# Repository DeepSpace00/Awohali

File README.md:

# ᎠᏬᎭᎵ (Awohali)

Pronounced (Ah-wo-ha-lee)

This project is archived. Current development has migrated to [Codeberg](https://codeberg.org/Fiducial-Systems/Awohali)

An open source hardware GNSS receiver station for measuring tropospheric precipitable water vapor.

A master's thesis project within Embry-Riddle Aeronautical University's Physical Science Department.

⚠️ WARNING This project is currently under development ⚠️

## Docs

https://deepspace00.github.io/Awohali/

## Hardware 

Preview with [KiCanvas](https://kicanvas.org/?github=https%3A%2F%2Fgithub.com%2FDeepSpace00%2FAwohali%2Ftree%2Fmain%2Fhardware%2Felectronics%2FmainBoard)

## Licenses

Documentation, firmware, hardware, and software are individually licensed. Terms and conditions apply within their respective folders.

**Documentation -** [Apache License 2.0](docs/LICENSE)

**Firmware/Software -** [The MIT License](firmware/LICENSE)

**Hardware -** [CERN-OHL-P v2 or later](hardware/LICENSE)

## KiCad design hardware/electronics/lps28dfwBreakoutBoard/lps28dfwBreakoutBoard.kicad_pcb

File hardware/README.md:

Copyright Madison Gleydura 2025.

This source describes Open Hardware and is licensed under the CERN-OHL-P v2

You may redistribute and modify this documentation and make products
using it under the terms of the [CERN-OHL-P v2](LICENSE).
This documentation is distributed WITHOUT ANY EXPRESS OR IMPLIED
WARRANTY, INCLUDING OF MERCHANTABILITY, SATISFACTORY QUALITY
AND FITNESS FOR A PARTICULAR PURPOSE. Please see the CERN-OHL-P v2
for applicable conditions

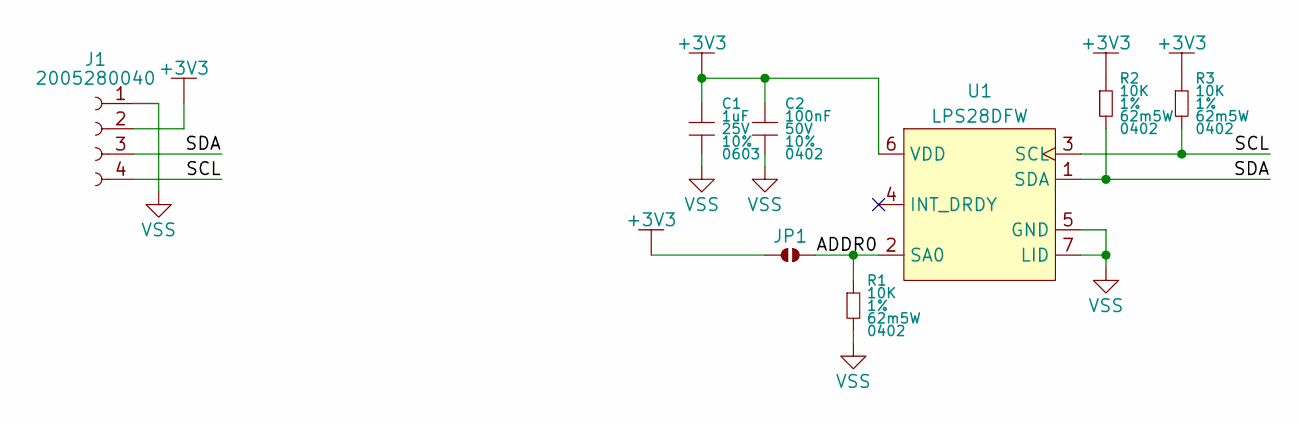
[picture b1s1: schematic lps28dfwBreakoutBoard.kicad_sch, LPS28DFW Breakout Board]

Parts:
C1: 1uF; GRT0603; Tolerance 10%; Voltage Rating 25V; MPN GRT188R71E105KE13D
C2: 100nF; GCM0402; Tolerance 10%; Voltage Rating 50V; MPN GRT155R71H104KE01D
J1: 2005280040; MPN 2005280040
JP1: SolderJumper-2_P1.3mm_Open_TrianglePad1.0x1.5mm
R1, R2, R3: 10K; CRCW0402; Tolerance 1%; Power Rating 62m5W; MPN CRCW040210K0FKED
U1: LPS28DFW; CCLGA7_LPS28DFWTR; MPN LPS28DFWTR

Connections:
+3V3: C1.1, C2.1, J1.2, JP1.1, R2.1, R3.1, U1.6 (VDD)
/ADDR0: JP1.2, R1.1, U1.2 (SA0)
/SCL: J1.4, R3.2, U1.3 (SCL)
/SDA: J1.3, R2.2, U1.1 (SDA)
VSS: C1.2, C2.2, J1.1, R1.2, U1.5 (GND), U1.7 (LID)

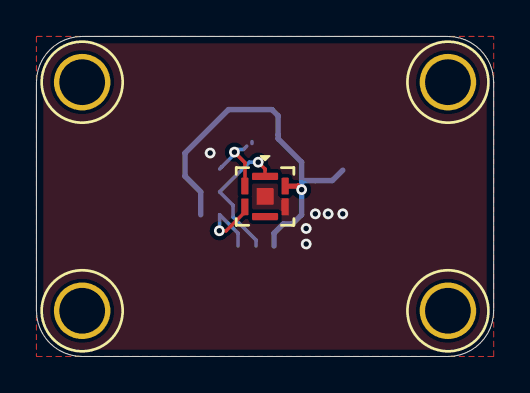
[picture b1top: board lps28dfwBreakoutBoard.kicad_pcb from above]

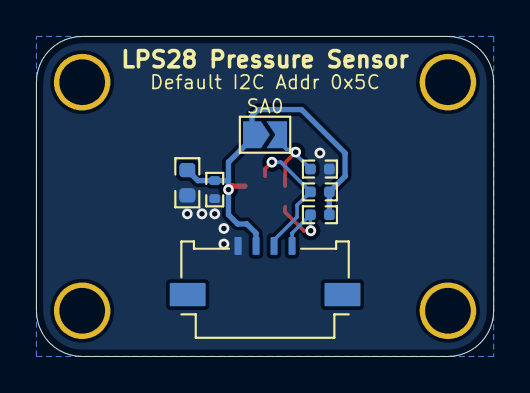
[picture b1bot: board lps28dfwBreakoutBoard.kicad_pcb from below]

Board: 2 copper layers, 25.4 x 17.8 mm, 8 parts (7 on the bottom side), 5 nets.

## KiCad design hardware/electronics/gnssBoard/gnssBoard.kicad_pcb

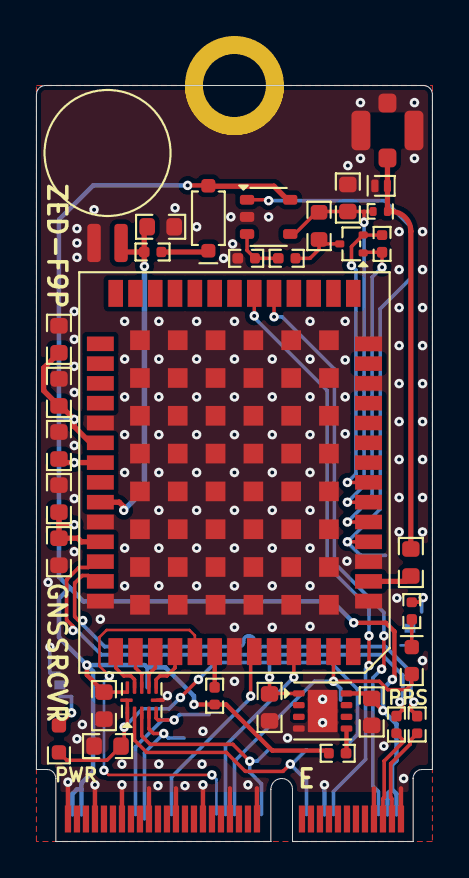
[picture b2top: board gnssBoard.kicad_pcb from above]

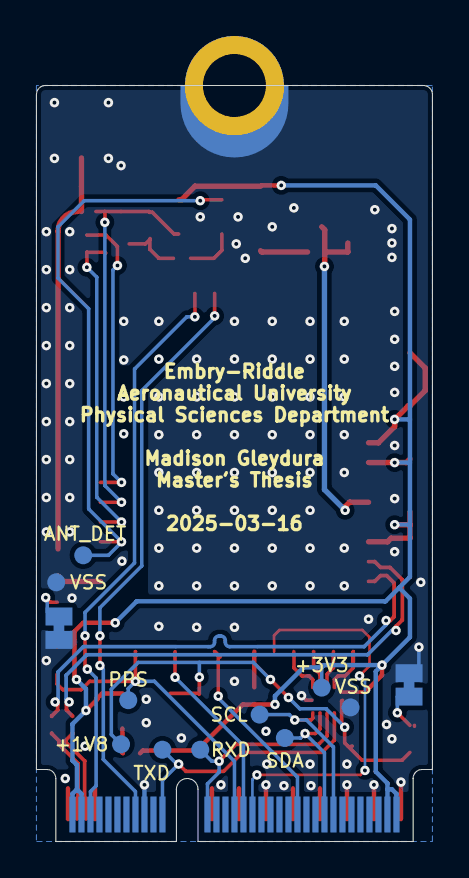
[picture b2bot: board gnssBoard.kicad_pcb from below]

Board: 4 copper layers, 22.0 x 42.0 mm, 48 parts (12 on the bottom side), 36 nets.

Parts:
AE1: CONMHF1-SMD-T; CONMHF1
BT1: MS621FE-FL11E
C1, C2, C9: 2.2uF; MLCC0603
C3: 47pF; MLCC0603
C4, C7: 1uF; MLCC0603
C5, C6, C8, C11, C12: 100nF; MLCC0603
C10: 10nF; MLCC0603
D1: LTST-C190KYKT; LTST-0603
D2: B0540WQ; SOD123
D3: PTVS4V5D1BLYL; SOD882
D4: LTST-C190KRKT; LTST-0603
J1: Standoff; M.2-Screw-Pad
J2: M.2_E_Key_PCB_Edge; M.2 E-Key
JP1, JP2: SolderJumper-2_P1.3mm_Bridged_Pad1.0x1.5mm
L1: 47nH; L_0402
Q1: DMG1013TQ-7; SOT23-3P50_160X160X75L22X22N
R1, R8, R11: 10K; CRCW0402
R4: 3K3; CRCW0402
R5: 10R; CRCW0603
R6: 100R; CRCW0402
R7, R9: 27R; CRCW0402
R10: 1K; CRCW0402
R12: 100K; CRCW0402
TP1: +3V3; TP_1mm
TP2: +1V8; TP_1mm
TP3, TP11: VSS; TP_1mm
TP4: SCL; TP_1mm
TP5: SDA; TP_1mm
TP6: TXD; TP_1mm
TP7: RXD; TP_1mm
TP9: PPS; TP_1mm
TP10: ANT_DET; TP_1mm
U1: AP7361E; UDFN8P65_300X300X60L25X45L
U2: TXS0104VxRUTR; RUT0012A
U3: ZED-F9P; ZED-F9P-04B_UBL
U4: OPA344; SOT23-5P95_280X300X110L40X38N

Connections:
+1V8: C2.1, C11.1, D1.1, TP2.1, U1.1 (OUT), U2.1 (VCCA), U2.12 (OE)
+3V3: C1.1, C4.1, C5.1, C6.1, C7.1, C8.1, C12.1, D2.1, J2.2 (3.3V), J2.4 (3.3V), J2.72 (3.3V), J2.74 (3.3V), R1.1, R11.1, TP1.1, U1.8 (IN), U2.11 (VCCB), U3.33 (VCC), U3.34 (VCC), U3.38 (V_USB), U4.5 (V+)
/ANT_DET: TP10.1, U3.4 (ANT_DET), U4.1
/ANT_IN: AE1.1 (A), C3.1, D3.2, L1.1
/ANT_OFF: Q1.1, R8.2, U3.5 (ANT_OFF)
/ANT_SHORT_N: C10.1, L1.2, R5.1, U3.6 (ANT_SHORT_N), U4.4 (-)
/EXTINT: J2.40 (VENDOR_DEFINED), U3.51 (EXTINT)
/GEOFENCE_STAT: J2.6 (~LED_1), U3.19 (GEOFENCE_STAT)
/HOST_D+: J2.3 (USB_D+), R7.1
/HOST_D-: J2.5 (USB_D-), R9.1
/PPS: D4.1, J2.38 (VENDOR_DEFINED), TP9.1, U3.53 (TIMEPULSE)
/RESET_N: J2.52 (~PERST0), U3.49 (RESET_N)
/RF_IN: C3.2, U3.2 (RF_IN)
/RTK_STAT: J2.16 (~LED_2), U3.20 (RTK_STAT)
/SCL_1V8: J2.60 (I2C_CLK), TP4.1, U2.5 (A4)
/SCL_3V3: U2.7 (B4), U3.45 (SCL)
/SDA_1V8: J2.58 (I2C_DATA), TP5.1, U2.4 (A3)
/SDA_3V3: U2.8 (B3), U3.44 (SDA)
/TX_RDY: J2.42 (VENDOR_DEFINED), U3.46 (TX_RDY)
/ZED_D+: R7.2, U3.40 (USB_DP)
/ZED_D-: R9.2, U3.39 (USB_DM)
/ZED_RXD_1V8: J2.32 (UART_TXD), TP7.1, U2.3 (A2)
/ZED_RXD_3V3: U2.9 (B2), U3.43 (RXD)
/ZED_TXD_1V8: J2.22 (UART_RXD), TP6.1, U2.2 (A1)
/ZED_TXD_3V3: U2.10 (B1), U3.42 (TXD)
unnamed: D1.2, JP1.2
unnamed: D2.2, R4.1
unnamed: D4.2, R6.2
unnamed: JP2.1, R6.1
unnamed: Q1.3, R5.2, R10.1
unnamed: R1.2, U1.5 (EN)
unnamed: R11.2, U3.47 (D_SEL)
unnamed: R10.2, R12.1, U4.3 (+)
VBAT: BT1.1, C9.1, R4.2, U3.36 (V_BCKP)
VCC_RF: Q1.2, R8.1, U3.7 (VCC_RF)
VSS: AE1.2 (Shield), BT1.2, C1.2, C2.2, C4.2, C5.2, C6.2, C7.2, C8.2, C9.2, C10.2, C11.2, C12.2, D3.1, J1.1, J2.1 (GND), J2.7 (GND), J2.18 (GND), J2.33 (GND), J2.39 (GND), J2.45 (GND), J2.51 (GND), J2.57 (GND), J2.63 (GND), J2.69 (GND), J2.75 (GND), JP1.1, JP2.2, R12.2, TP3.1, TP11.1, U1.4 (GND), U1.9 (GND), U2.6 (GND), U3.1 (GND), U3.3 (GND), U3.12 (GND), U3.14 (GND), U3.32 (GND), U3.37 (GND), U3.41 (GND), U3.48 (GND), U3.55 (PGND), U3.56 (PGND), U3.57 (PGND), U3.58 (PGND), U3.59 (PGND), U3.60 (PGND), U3.61 (PGND), U3.62 (PGND), U3.63 (PGND), U3.64 (PGND), U3.65 (PGND), U3.66 (PGND), U3.67 (PGND), U3.68 (PGND), U3.69 (PGND), U3.70 (PGND), U3.71 (PGND), U3.72 (PGND), U3.73 (PGND), U3.74 (PGND), U3.75 (PGND), U3.76 (PGND), U3.77 (PGND), U3.78 (PGND), U3.79 (PGND), U3.80 (PGND), U3.81 (PGND), U3.82 (PGND), U3.83 (PGND), U3.84 (PGND), U3.85 (PGND), U3.86 (PGND), U3.87 (PGND), U3.88 (PGND), U3.89 (PGND), U3.90 (PGND), U3.91 (PGND), U3.92 (PGND), U3.93 (PGND), U3.94 (PGND), U3.95 (PGND), U3.96 (PGND), U3.97 (PGND), U3.98 (PGND), U3.99 (PGND), U3.100 (PGND), U3.101 (PGND), U3.102 (PGND), U4.2 (V-)

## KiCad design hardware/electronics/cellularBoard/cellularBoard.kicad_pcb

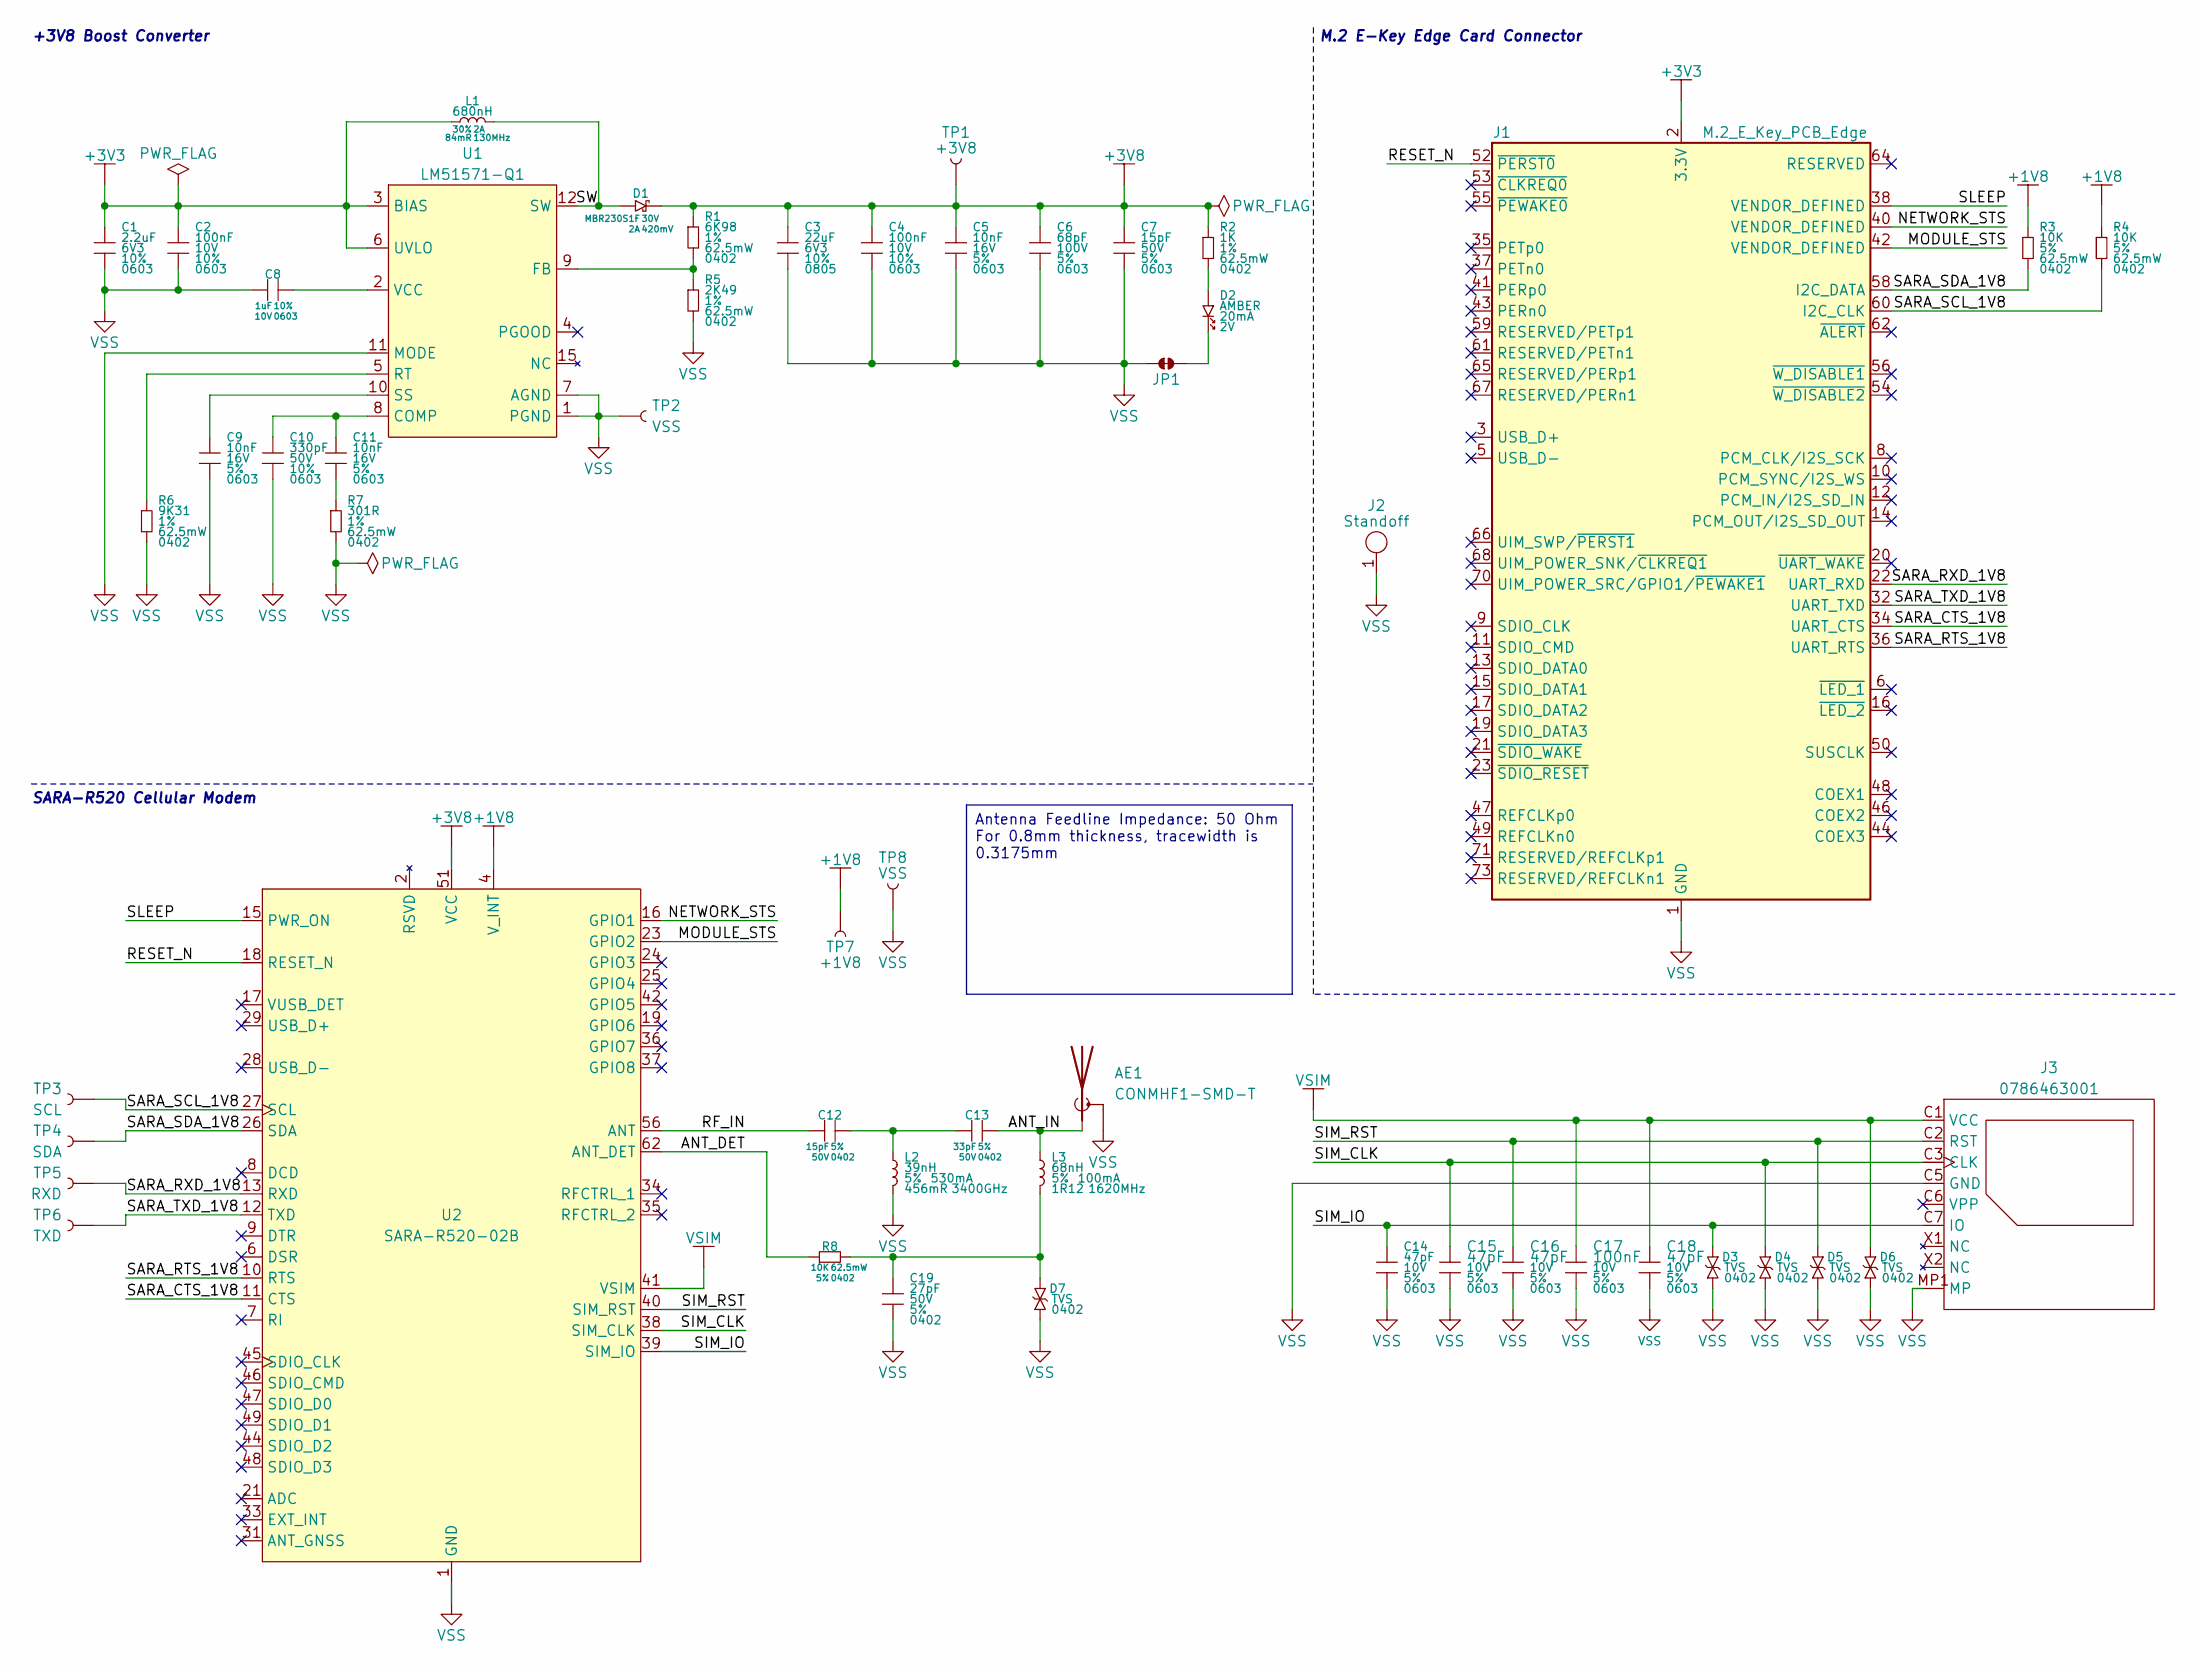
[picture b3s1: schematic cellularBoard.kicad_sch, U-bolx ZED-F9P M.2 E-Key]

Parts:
AE1: CONMHF1-SMD-T; CONMHF1; MPN CONMHF1-SMD-T
C1: 2.2uF; MLCC0603; Tolerance 10%; Voltage Rating 6V3; MPN KAM15AR70J225KT
C2, C4: 100nF; MLCC0603; Tolerance 10%; Voltage Rating 10V; MPN KAM15AR71A104KT
C3: 22uF; MLCC0805; Tolerance 10%; Voltage Rating 6V3; MPN KAM21AT70J226KU
C5, C9, C11: 10nF; MLCC0603; Tolerance 5%; Voltage Rating 16V; MPN KAM15AR71C103JT
C6: 68pF; MLCC0603; Tolerance 5%; Voltage Rating 100V; MPN KAM15ACG2A680JT
C7: 15pF; MLCC0603; Tolerance 5%; Voltage Rating 50V; MPN KAM15ACG1H150JT
C8: 1uF; MLCC0603; Tolerace 10%; Voltage Rating 10V; MPN KAM15AR71A105KT
C10: 330pF; MLCC0603; Tolerance 10%; Voltage Rating 50V; MPN 06035C331K4T2A
C12: 15pF; MLCC0402; Tolerace 5%; Voltage Rating 50V; MPN GCM1555C1H150JA16J
C13: 33pF; MLCC0402; Tolerace 5%; Voltage Rating 50V; MPN GCM1555C1H330JA16J
C14, C15, C16, C18: 47pF; MLCC0603; Tolerance 5%; Voltage Rating 10V; MPN 06035C470JAT2A
C17: 100nF; MLCC0603; Tolerance 5%; Voltage Rating 10V; MPN 06035C470JAT2A
C19: 27pF; MLCC0402; Tolerance 5%; Voltage Rating 50V; MPN GCM1555C1H270JA16J
D1: MBR230S1F; SOD123F; Reverse Voltage 30V; Forward Voltage 420mV; MPN MBR230S1F-7
D2: LTST-C190KYKT; LTST-0603; Forward Voltage 2V; MPN LTST-C190KYKT
D3, D4, D5, D6, D7: TVS; XDFN2P65_100X60X50L50X25L; MPN DESD24VF1BLQ-7B
J1: M.2_E_Key_PCB_Edge; M.2 E-Key; MPN N/A
J2: Standoff; M.2-Screw-Pad
J3: 0786463001; 786463001; MPN 0786463001
JP1: SolderJumper-2_P1.3mm_Bridged_Pad1.0x1.5mm
L1: 680nH; L_0806; Tolerance 30%; Current Rating 2A; MPN 744383430068
L2: 39nH; L_0402; Tolerance 5%; Current Rating 530mA; MPN LQW15AN39NJ8ZD
L3: 68nH; L_0402; Tolerance 5%; Current Rating 100mA; MPN 744765168A
R1: 6K98; CRCW0402; Tolerance 1%; Power Rating 62.5mW; MPN CRCW04026K98FKED
R2: 1K; CRCW0402; Tolerance 1%; Power Rating 62.5mW; MPN CRCW04021K00FKED
R3, R4, R8: 10K; CRCW0402; Tolerance 5%; Power Rating 62.5mW; MPN CRCW040210K0JNED
R5: 2K49; CRCW0402; Tolerance 1%; Power Rating 62.5mW; MPN CRCW04022K49FKED
R6: 9K31; CRCW0402; Tolerance 1%; Power Rating 62.5mW; MPN CRCW04029K31FKED
R7: 301R; CRCW0402; Tolerance 1%; Power Rating 62.5mW; MPN CRCW0402301RFKED
TP1: +3V8; TP_1mm
TP2, TP8: VSS; TP_1mm
TP3: SCL; TP_1mm
TP4: SDA; TP_1mm
TP5: RXD; TP_1mm
TP6: TXD; TP_1mm
TP7: +1V8; TP_1mm
U1: LM51571-Q1; RTE0016K; MPN LM51571QRTERQ1
U2: SARA-R520-02B; SARA-R52X_UBL; MPN SARA-R520-02B

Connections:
+1V8: R3.1, R4.1, TP7.1, U2.4 (V_INT)
+3V3: C1.1, C2.1, J1.2 (3.3V), J1.4 (3.3V), J1.72 (3.3V), J1.74 (3.3V), L1.1, U1.3 (BIAS), U1.6 (UVLO)
+3V8: C3.1, C4.1, C5.1, C6.1, C7.1, D1.2, R1.1, R2.1, TP1.1, U2.51 (VCC), U2.52 (VCC), U2.53 (VCC)
/ANT_DET: R8.1, U2.62 (ANT_DET)
/ANT_IN: AE1.1 (A), C13.2, L3.1
/MODULE_STS: J1.42 (VENDOR_DEFINED), U2.23 (GPIO2)
/NETWORK_STS: J1.40 (VENDOR_DEFINED), U2.16 (GPIO1)
/RESET_N: J1.52 (~PERST0), U2.18 (RESET_N)
/RF_IN: C12.1, U2.56 (ANT)
/SARA_CTS_1V8: J1.34 (UART_CTS), U2.11 (CTS)
/SARA_RTS_1V8: J1.36 (UART_RTS), U2.10 (RTS)
/SARA_RXD_1V8: J1.22 (UART_RXD), TP5.1, U2.13 (RXD)
/SARA_SCL_1V8: J1.60 (I2C_CLK), R4.2, TP3.1, U2.27 (SCL)
/SARA_SDA_1V8: J1.58 (I2C_DATA), R3.2, TP4.1, U2.26 (SDA)
/SARA_TXD_1V8: J1.32 (UART_TXD), TP6.1, U2.12 (TXD)
/SIM_CLK: C15.1, D4.2, J3.C3 (CLK), U2.38 (SIM_CLK)
/SIM_IO: C14.1, D3.2, J3.C7 (IO), U2.39 (SIM_IO)
/SIM_RST: C16.1, D5.2, J3.C2 (RST), U2.40 (SIM_RST)
/SLEEP: J1.38 (VENDOR_DEFINED), U2.15 (PWR_ON)
/SW: D1.1, L1.2, U1.12 (SW), U1.13 (SW), U1.14 (SW)
unnamed: C11.2, R7.1
unnamed: C12.2, C13.1, L2.1
unnamed: C19.1, D7.2, L3.2, R8.2
unnamed: D2.1, R2.2
unnamed: D2.2, JP1.2
unnamed: C10.1, C11.1, U1.8 (COMP)
unnamed: R1.2, R5.1, U1.9 (FB)
unnamed: R6.1, U1.5 (RT)
unnamed: C9.1, U1.10 (SS)
unnamed: C8.2, U1.2 (VCC)
VSIM: C17.1, C18.1, D6.2, J3.C1 (VCC), U2.41 (VSIM)
VSS: AE1.2 (Shield), C1.2, C2.2, C3.2, C4.2, C5.2, C6.2, C7.2, C8.1, C9.2, C10.2, C14.2, C15.2, C16.2, C17.2, C18.2, C19.2, D3.1, D4.1, D5.1, D6.1, D7.1, J1.1 (GND), J1.7 (GND), J1.18 (GND), J1.33 (GND), J1.39 (GND), J1.45 (GND), J1.51 (GND), J1.57 (GND), J1.63 (GND), J1.69 (GND), J1.75 (GND), J2.1, J3.C5 (GND), J3.MP1 (MP), J3.MP2 (MP), J3.MP3 (MP), J3.MP4 (MP), J3.MP5 (MP), J3.MP6 (MP), JP1.1, L2.2, R5.2, R6.2, R7.2, TP2.1, TP8.1, U1.1 (PGND), U1.7 (AGND), U1.11 (MODE), U1.16 (PGND), U1.17 (AGND), U2.1 (GND), U2.3 (GND), U2.5 (GND), U2.14 (GND), U2.20 (GND), U2.22 (GND), U2.30 (GND), U2.32 (GND), U2.43 (GND), U2.50 (GND), U2.54 (GND), U2.55 (GND), U2.57 (GND), U2.58 (GND), U2.59 (GND), U2.60 (GND), U2.61 (GND), U2.63 (GND), U2.64 (GND), U2.65 (GND), U2.66 (GND), U2.67 (GND), U2.68 (GND), U2.69 (GND), U2.70 (GND), U2.71 (GND), U2.72 (GND), U2.73 (GND), U2.74 (GND), U2.75 (GND), U2.76 (GND), U2.77 (GND), U2.78 (GND), U2.79 (GND), U2.80 (GND), U2.81 (GND), U2.82 (GND), U2.83 (GND), U2.84 (GND), U2.85 (GND), U2.86 (GND), U2.87 (GND), U2.88 (GND), U2.89 (GND), U2.90 (GND), U2.91 (GND), U2.92 (GND), U2.93 (GND), U2.94 (GND), U2.95 (GND), U2.96 (GND)

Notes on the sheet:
SARA-R520 Cellular Modem
+3V8 Boost Converter
M.2 E-Key Edge Card Connector
Antenna Feedline Impedance: 50 Ohm For 0.8mm thickness, tracewidth is 0.3175mm

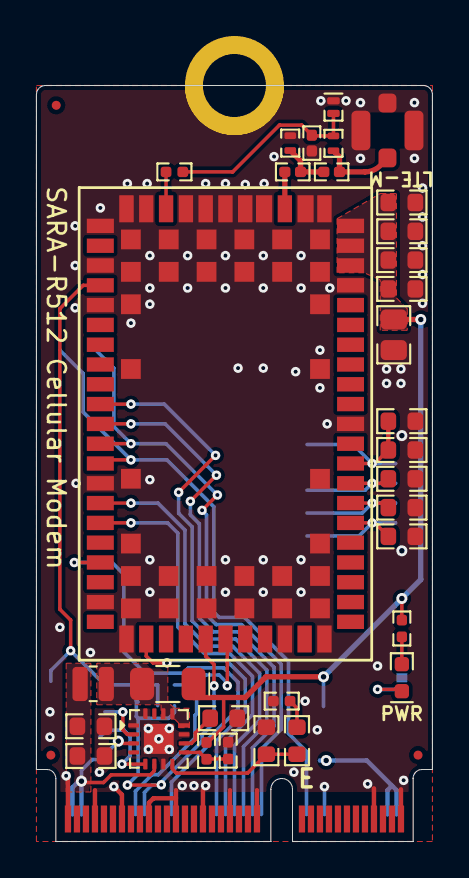
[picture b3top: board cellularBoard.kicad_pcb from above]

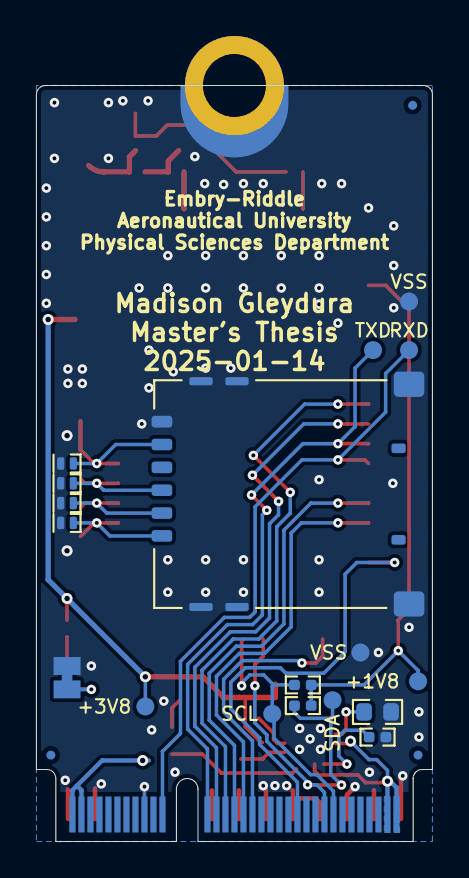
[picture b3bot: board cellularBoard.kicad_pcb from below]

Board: 4 copper layers, 22.0 x 42.0 mm, 52 parts (18 on the bottom side), 32 nets.

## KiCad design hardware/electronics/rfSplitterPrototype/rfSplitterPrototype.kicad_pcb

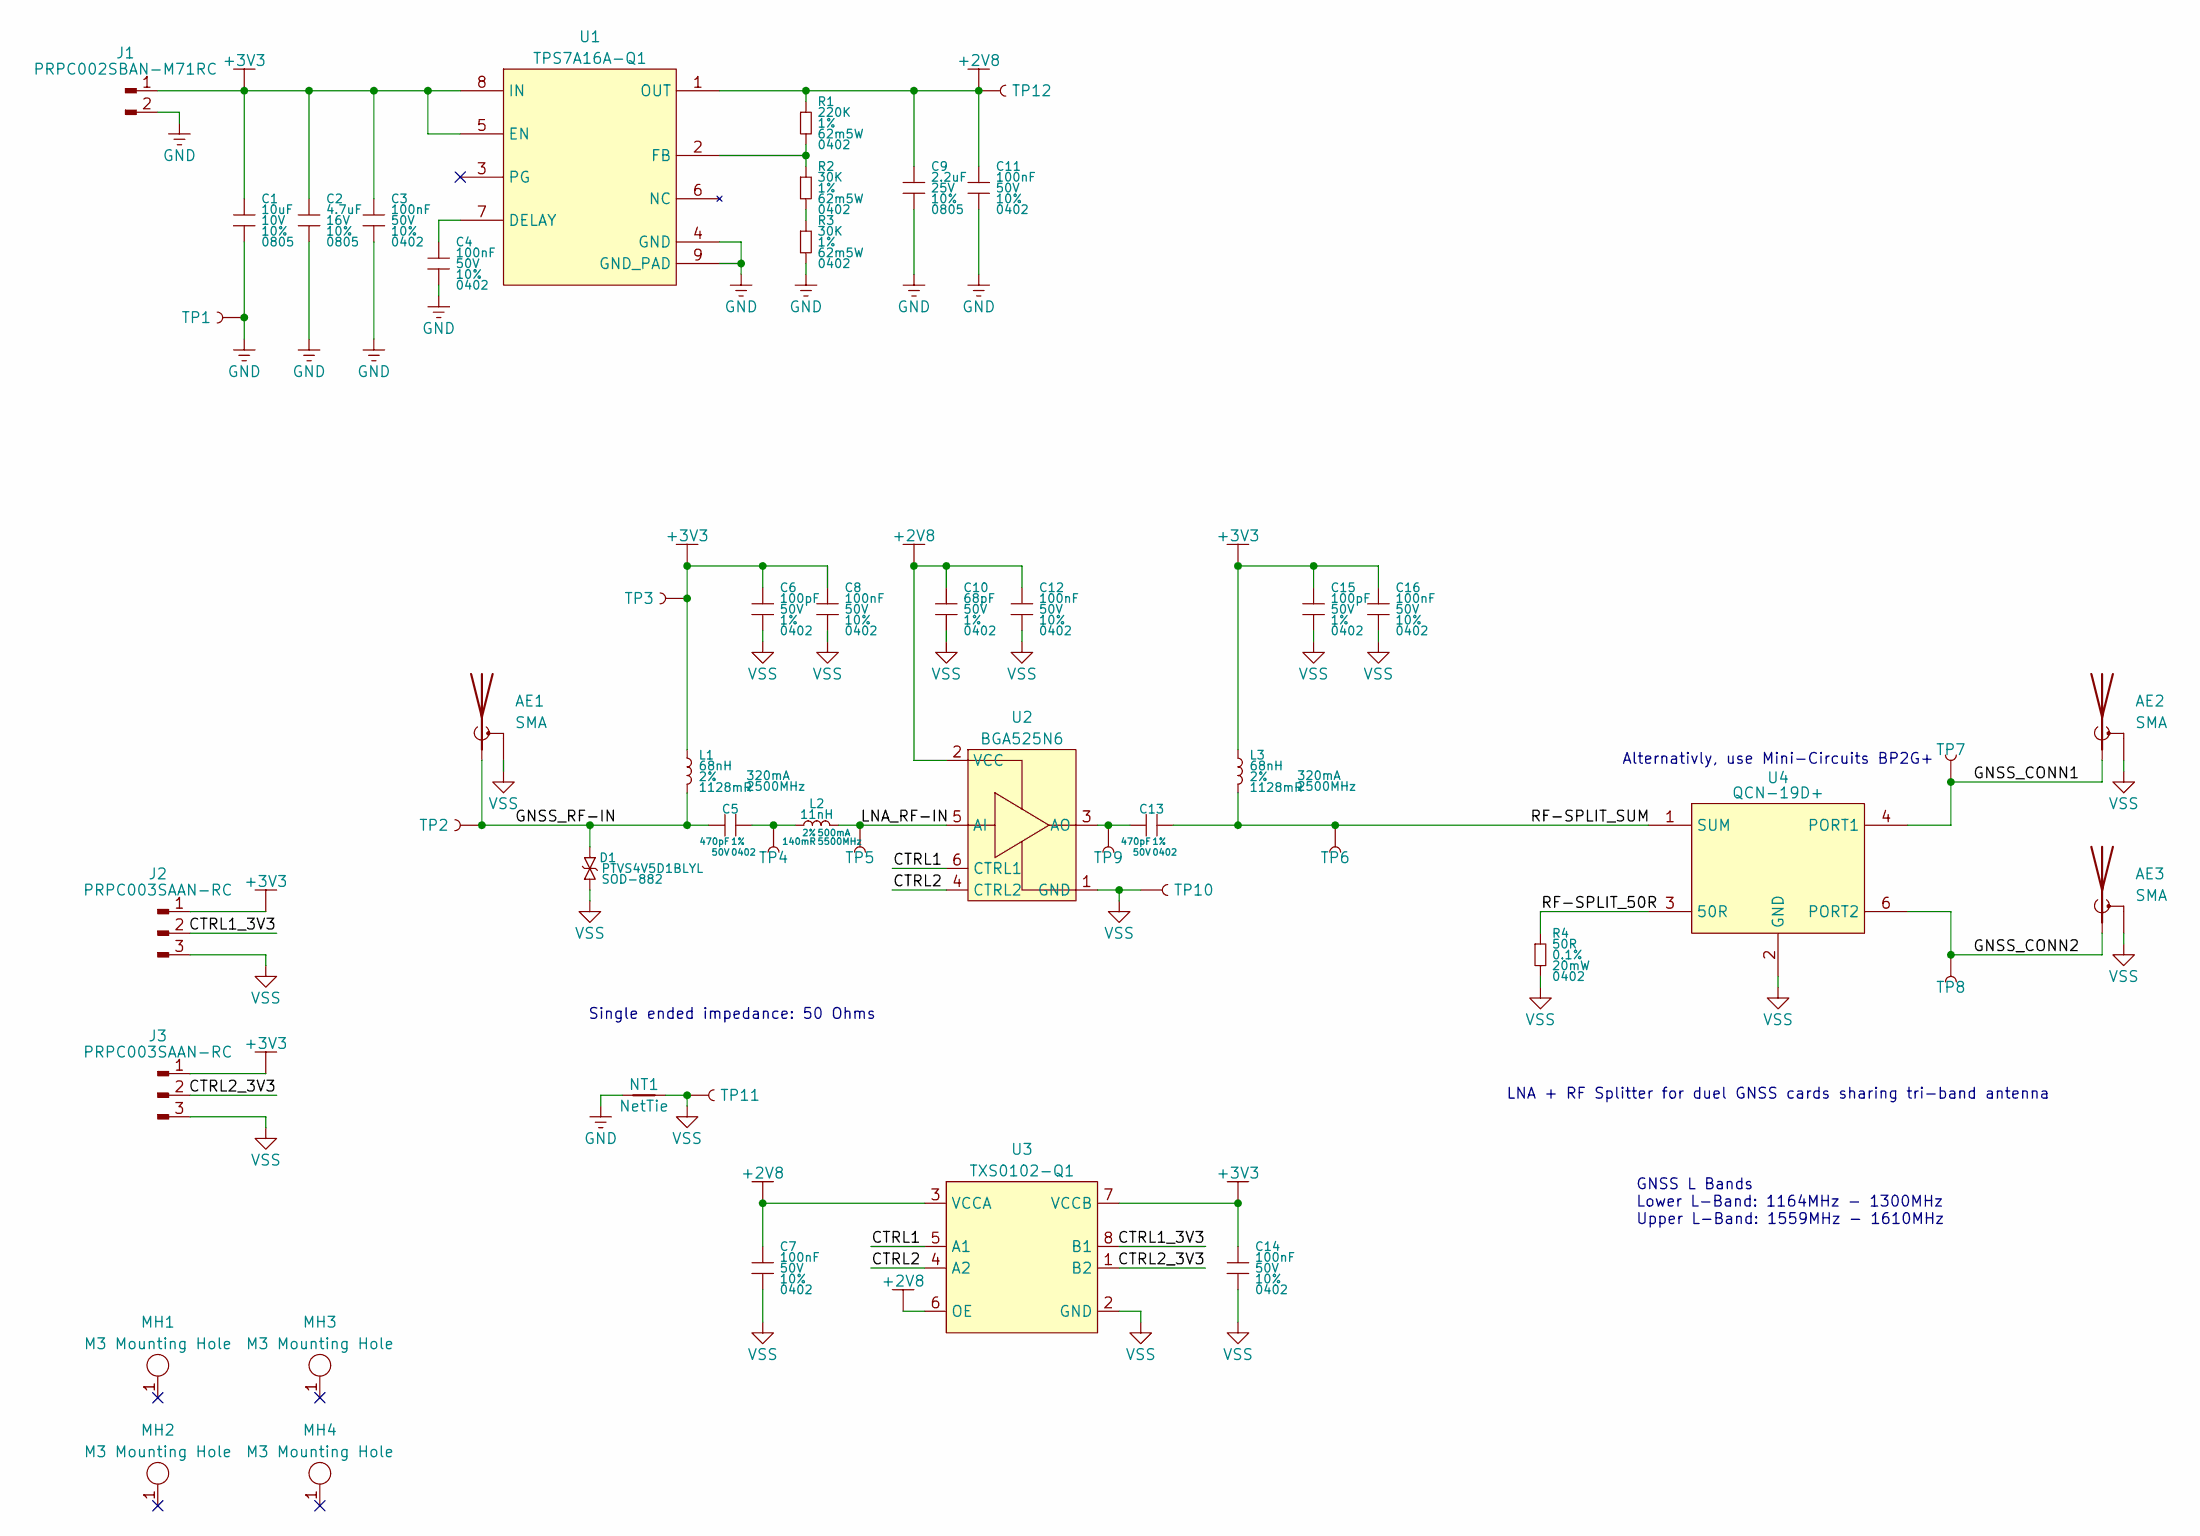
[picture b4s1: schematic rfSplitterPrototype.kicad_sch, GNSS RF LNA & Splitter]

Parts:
AE1, AE2, AE3: SMA; 0732511153; MPN CONSMA002-G
C1: 10uF; GCM0805; Tolerance 10%; Voltage Rating 10V; MPN GCM21BR71A106KE22L
C2: 4.7uF; GCM0805; Tolerance 10%; Voltage Rating 16V; MPN GRT21BR71C475KE13L
C3, C4, C7, C8, C11, C12, C14, C16: 100nF; GCM0402; Tolerance 10%; Voltage Rating 50V; MPN GRT155R71H104KE01D
C5, C13: 470pF; GCM0402; Tolerance 1%; Voltage Rating 50V; MPN GCM1555C1H471FA16D
C6, C15: 100pF; GCM0402; Tolerance 1%; Voltage Rating 50V; MPN GCM1555C1H101FA16D
C9: 2.2uF; GCM0805; Tolerance 10%; Voltage Rating 25V; MPN GRT21BR71E225KE13L
C10: 68pF; GCM0402; Tolerance 1%; Voltage Rating 50V; MPN GCM1555C1H101FA16D
D1: PTVS4V5D1BLYL; SOD882; MPN PTVS4V5D1BLYL
J1: PRPC002SBAN-M71RC; conn_01x02_254_right_angle; MPN PRPC002SBAN-M71RC
J2, J3: PRPC003SAAN-RC; conn_01x03_254; MPN PRPC003SAAN-RC
L1, L3: 68nH; L_0402; Tolerance 2%; Current Rating 320mA; MPN LQW15AN68NG8ZD
L2: 11nH; L_0402; Tolerance 2%; Current Rating 500mA; MPN LQW15AN11NG0ZD
MH1, MH2, MH3, MH4: M3 Mounting Hole; M3_NPTH
NT1: NetTie; NetTie-2_SMD_Pad1.0mm
R1: 220K; CRCW0402; Tolerance 1%; Power Rating 62m5W; MPN CRCW0402220KFKED
R2, R3: 30K; CRCW0402; Tolerance 1%; Power Rating 62m5W; MPN CRCW040230K0FKED
R4: 50R; CRCW0402; Tolerance 0.1%; Power Rating 20mW; MPN FC0402E50R0BST1
TP1, TP10, TP11: RCWCTE; TP_RCW; MPN RCWCTE
TP2, TP3, TP4, TP5, TP6, TP7, TP8, TP9, TP12: TP_2mm; MPN N/A
U1: TPS7A16A-Q1; HVSSOP65P490X110-8; MPN TPS7A1601AQDGNRQ1
U2: BGA525N6; XDFN110X70X37-6; MPN BGA525N6E6327XTSA1
U3: TXS0102-Q1; VSSOP50P310X90-8; MPN TXS0102QDCURQ1
U4: QCN-19D+; SON99P320X160X89-6; MPN QCN-19D+

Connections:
+2V8: C7.1, C9.1, C10.1, C11.1, C12.1, R1.1, TP12.1, U1.1 (OUT), U2.2 (VCC), U3.3 (VCCA), U3.6 (OE)
+3V3: C1.1, C2.1, C3.1, C6.1, C8.1, C14.1, C15.1, C16.1, J1.1, J2.1, J3.1, L1.1, L3.1, TP3.1, U1.5 (EN), U1.8 (IN), U3.7 (VCCB)
/CTRL1: U2.6 (CTRL1), U3.5 (A1)
/CTRL1_3V3: J2.2, U3.8 (B1)
/CTRL2: U2.4 (CTRL2), U3.4 (A2)
/CTRL2_3V3: J3.2, U3.1 (B2)
/GNSS_CONN1: AE2.1 (A), TP7.1, U4.4 (PORT1)
/GNSS_CONN2: AE3.1 (A), TP8.1, U4.6 (PORT2)
/GNSS_RF-IN: AE1.1 (A), C5.1, D1.2, L1.2, TP2.1
/LNA_RF-IN: L2.2, TP5.1, U2.5 (AI)
/RF-SPLIT_50R: R4.1, U4.3 (50R)
/RF-SPLIT_SUM: C13.2, L3.2, TP6.1, U4.1 (SUM)
GND: C1.2, C2.2, C3.2, C4.2, C9.2, C11.2, J1.2, NT1.1, R3.2, TP1.1, U1.4 (GND), U1.9 (GND_PAD)
unnamed: C5.2, L2.1, TP4.1
unnamed: R2.2, R3.1
unnamed: C4.1, U1.7 (DELAY)
unnamed: R1.2, R2.1, U1.2 (FB)
unnamed: C13.1, TP9.1, U2.3 (AO)
VSS: AE1.2 (Shield), AE2.2 (Shield), AE3.2 (Shield), C6.2, C7.2, C8.2, C10.2, C12.2, C14.2, C15.2, C16.2, D1.1, J2.3, J3.3, NT1.2, R4.2, TP10.1, TP11.1, U2.1 (GND), U3.2 (GND), U4.2 (GND), U4.5 (GND)

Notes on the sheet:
Alternativly, use Mini-Circuits BP2G+
LNA + RF Splitter for duel GNSS cards sharing tri-band antenna
Single ended impedance: 50 Ohms
GNSS L Bands Lower L-Band: 1164MHz - 1300MHz Upper L-Band: 1559MHz - 1610MHz

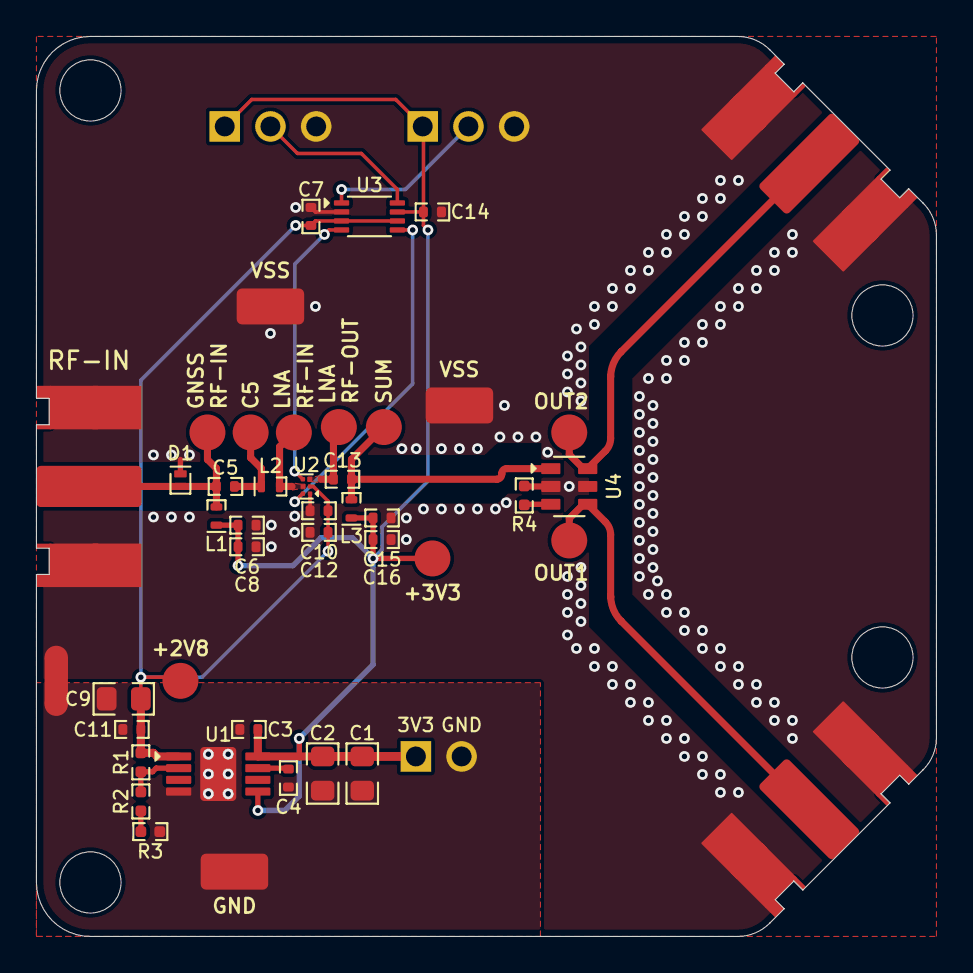
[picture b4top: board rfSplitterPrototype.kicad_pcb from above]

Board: 4 copper layers, 50.0 x 50.0 mm, 51 parts (0 on the bottom side), 19 nets.

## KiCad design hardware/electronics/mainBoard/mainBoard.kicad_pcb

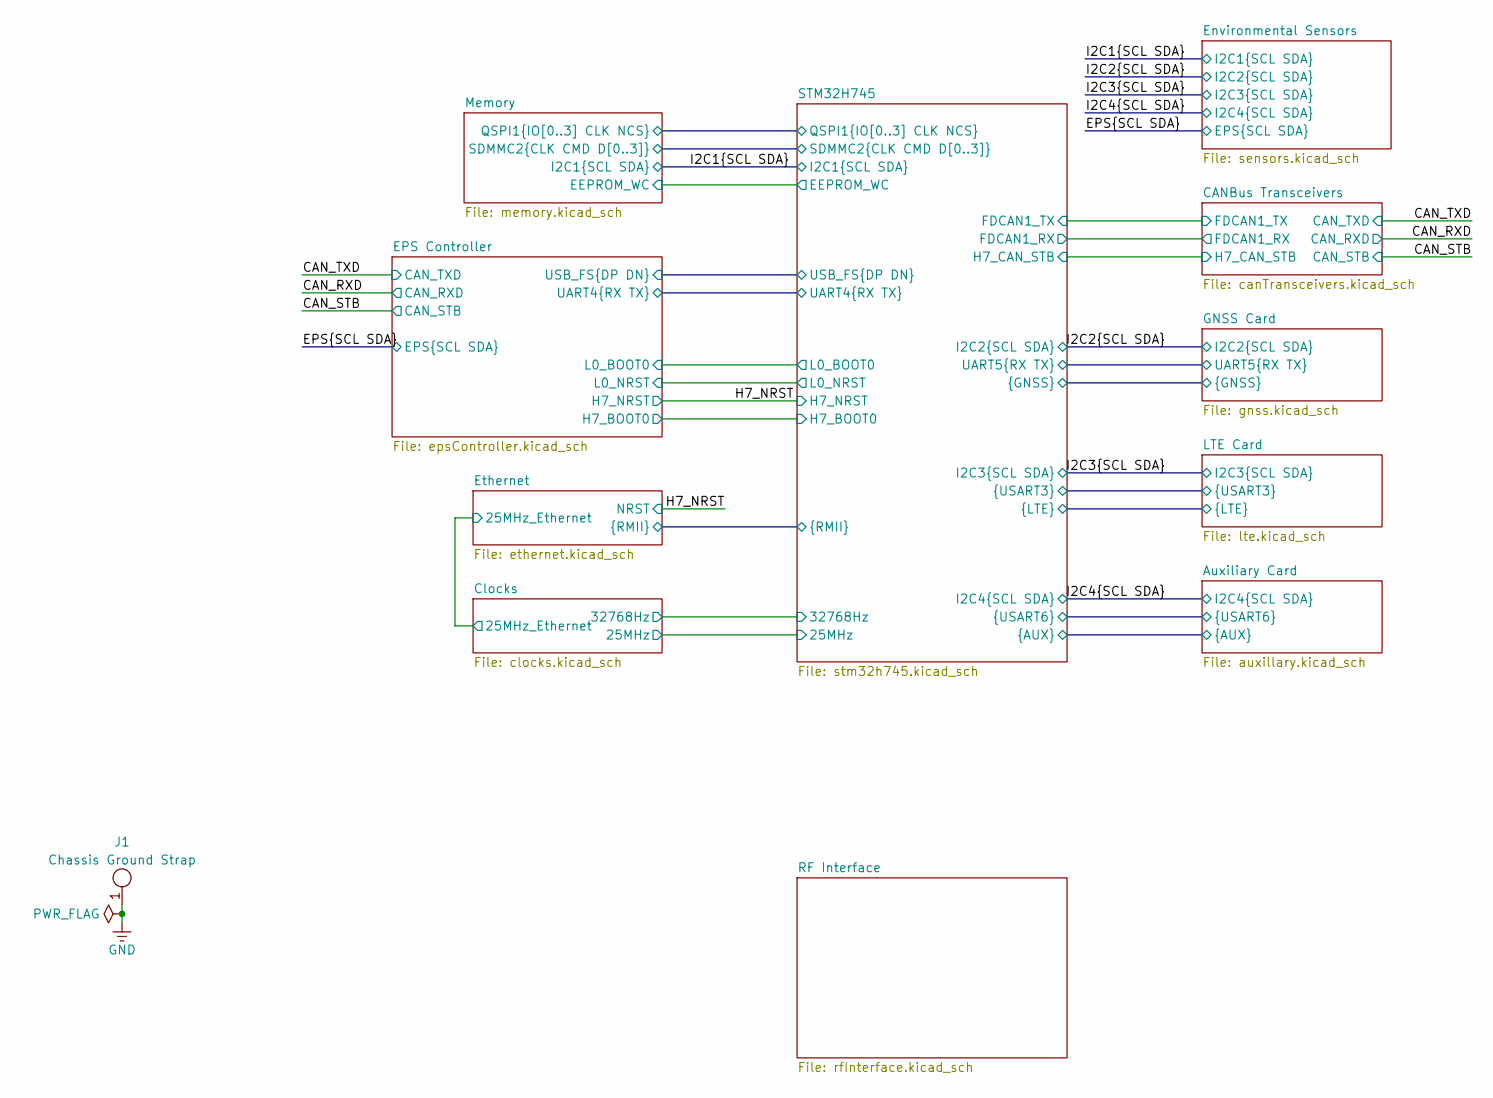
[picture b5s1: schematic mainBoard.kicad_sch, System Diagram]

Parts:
J1: Chassis Ground Strap; M4.5-MH; MPN L-1011-3

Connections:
GND: J1.1; also elsewhere on the board
